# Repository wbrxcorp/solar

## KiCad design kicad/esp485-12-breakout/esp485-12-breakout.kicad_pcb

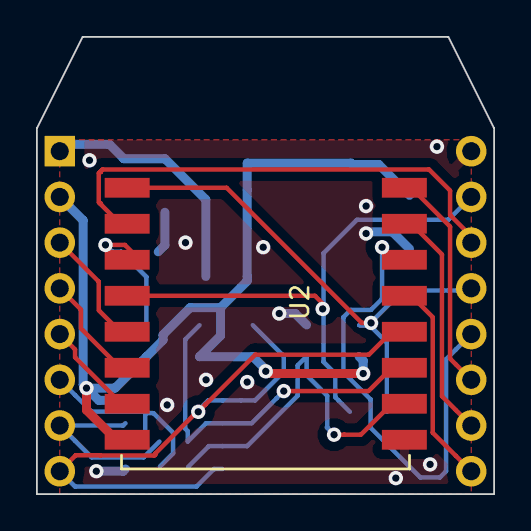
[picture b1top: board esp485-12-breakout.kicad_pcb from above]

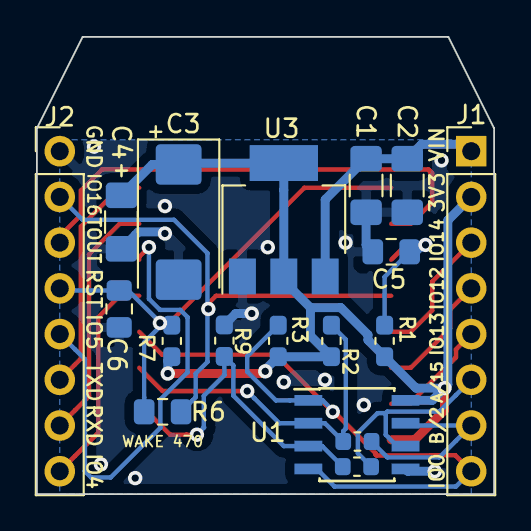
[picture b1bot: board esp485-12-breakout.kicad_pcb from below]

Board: 2 copper layers, 25.4 x 25.4 mm, 19 parts (18 on the bottom side), 19 nets.

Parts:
C1, C2, C4: C; C_1206_3216Metric_Pad1.42x1.75mm_HandSolder
C3: C; CP_EIA-7343-15_Kemet-W_Pad2.25x2.55mm_HandSolder
C5, C6: C; C_0805_2012Metric_Pad1.15x1.40mm_HandSolder
J1, J2: Conn_01x08; PinHeader_1x08_P2.54mm_Vertical
R1, R2, R3, R7, R9: 10K; R_0603_1608Metric_Pad1.05x0.95mm_HandSolder
R4, R8: 0; R_0603_1608Metric
R6: 1k; R_0805_2012Metric_Pad1.15x1.40mm_HandSolder
U1: MAX3485; SOIC-8_3.9x4.9mm_P1.27mm
U2: ESP-12; ESP-12E_SMD_NO_UNUSED_PAD
U3: AMS1117-3.3; SOT-223-3_TabPin2

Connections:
+3V3: C3.1, C4.1, J1.2, R1.1, R2.1, R3.1, R7.1, U1.8, U2.8, U3.2
A: J1.6, R4.1, U1.6
B: J1.7, R8.1, U1.7
EN: C5.1, R1.2, U2.3
GND: C1.2, C2.2, C3.2, C4.2, C5.2, C6.2, J2.1, R9.2, U1.5, U2.9, U3.1
IO0: J1.8, R3.2, U1.1, U1.4, U2.12
IO2: R2.2, R8.2, U1.2, U2.11
IO4: J2.8, U2.13
IO5: J2.5, U2.14
IO12: J1.4, U2.6
IO13: J1.5, U2.7
IO14: J1.3, U2.5
IO15: R4.2, R9.1, U1.3, U2.10
IO16: J2.2, R6.2, U2.4
RST: C6.1, J2.4, R6.1, R7.2, U2.1
RXD: J2.7, U2.15
TOUT: J2.3, U2.2
TXD: J2.6, U2.16
VCC: C1.1, C2.1, J1.1, U3.3

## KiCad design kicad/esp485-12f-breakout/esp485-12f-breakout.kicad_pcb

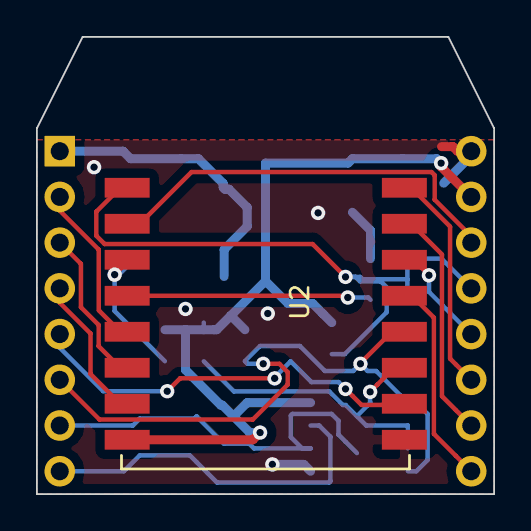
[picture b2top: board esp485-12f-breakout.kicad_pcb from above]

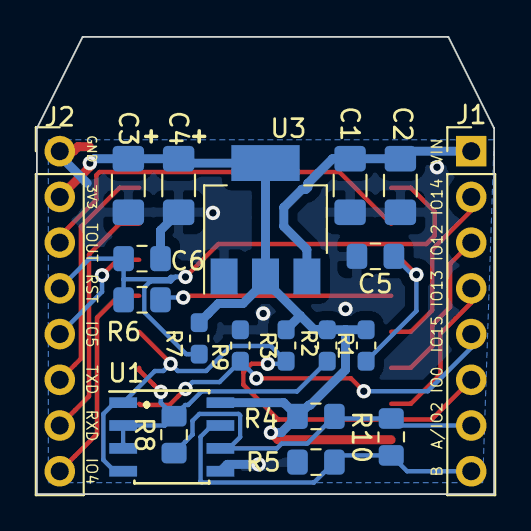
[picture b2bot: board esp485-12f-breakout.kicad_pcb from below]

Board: 2 copper layers, 25.4 x 25.4 mm, 21 parts (20 on the bottom side), 19 nets.

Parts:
C1, C2, C3, C4: C; C_1206_3216Metric_Pad1.42x1.75mm_HandSolder
C5, C6: 0.1uF; C_0805_2012Metric_Pad1.15x1.40mm_HandSolder
J1, J2: Conn_01x08; PinHeader_1x08_P2.54mm_Vertical
R1, R2, R3, R7, R9: 10K; R_0603_1608Metric_Pad1.05x0.95mm_HandSolder
R4, R5: 20K; R_0805_2012Metric_Pad1.15x1.40mm_HandSolder
R6: 1k; R_0805_2012Metric_Pad1.15x1.40mm_HandSolder
R8: 0; R_0805_2012Metric_Pad1.15x1.40mm_HandSolder
R10: 100; R_0805_2012Metric_Pad1.15x1.40mm_HandSolder
U1: MAX3485; SOIC-8_3.9x4.9mm_P1.27mm
U2: ESP-12F; ESP-12E_SMD_NO_UNUSED_PAD
U3: AMS1117-3.3; SOT-223-3_TabPin2

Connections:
+3V3: C3.1, C4.1, J2.2, R1.2, R2.1, R3.1, R4.1, R7.1, U1.8, U2.8, U3.2
/A: J1.7, R4.2, R8.1, R10.2, U1.6
/B: J1.8, R5.1, R10.1, U1.7
/EN: C5.1, R1.1, U2.3
/IO0: J1.6, R3.2, U1.1, U1.4, U2.12
/IO2: R2.2, R8.2, U1.2, U1.3, U2.11
/IO4: J2.8, U2.13
/IO5: J2.5, U2.14
/IO12: J1.3, U2.6
/IO13: J1.4, U2.7
/IO14: J1.2, U2.5
/IO15: J1.5, R9.1, U2.10
/RST: C6.1, J2.4, R6.2, R7.2, U2.1
/RXD: J2.7, U2.15
/TOUT: J2.3, U2.2
/TXD: J2.6, U2.16
GND: C1.2, C2.2, C3.2, C4.2, C5.2, C6.2, J2.1, R5.2, R9.2, U1.5, U2.9, U3.1
unnamed: R6.1, U2.4
VCC: C1.1, C2.1, J1.1, U3.3

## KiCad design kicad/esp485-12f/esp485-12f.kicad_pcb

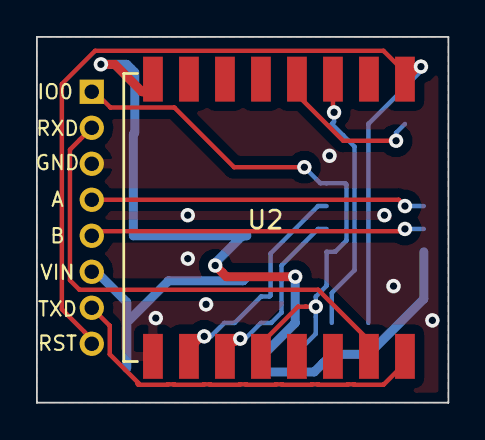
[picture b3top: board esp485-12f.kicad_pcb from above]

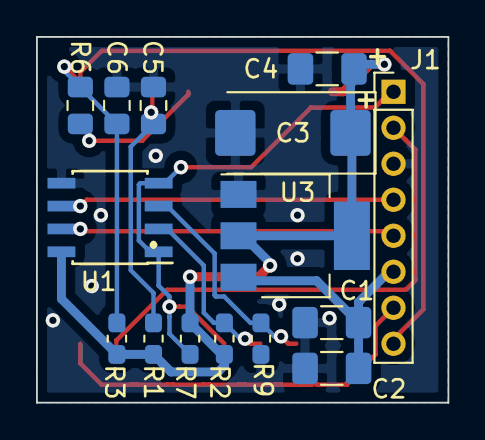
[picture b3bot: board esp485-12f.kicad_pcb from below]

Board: 2 copper layers, 22.9 x 20.3 mm, 16 parts (15 on the bottom side), 13 nets.

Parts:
C1, C2, C4: C; C_1206_3216Metric_Pad1.42x1.75mm_HandSolder
C3: C; CP_EIA-7343-15_Kemet-W_Pad2.25x2.55mm_HandSolder
C5, C6: C; C_0805_2012Metric_Pad1.15x1.40mm_HandSolder
J1: Conn_01x08; PinHeader_1x08_P2.00mm_Vertical
R1, R2, R3, R7, R9: 10K; R_0603_1608Metric_Pad1.05x0.95mm_HandSolder
R6: 1K; R_0805_2012Metric_Pad1.15x1.40mm_HandSolder
U1: MAX3485; SOIC-8_3.9x4.9mm_P1.27mm
U2: ESP-12F; ESP-12E_SMD_NO_UNUSED_PAD
U3: AMS1117-3.3; SOT-223-3_TabPin2

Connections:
+3V3: C3.1, C4.1, R1.2, R2.2, R3.2, R7.2, U1.8, U2.8, U3.2
A: J1.4, U1.6
B: J1.5, U1.7
EN: C5.1, R1.1, U2.3
GND: C1.2, C2.2, C3.2, C4.2, C5.2, C6.2, J1.3, R9.1, U1.5, U2.9, U3.1
IO0: J1.1, R7.1, U1.1, U1.4, U2.12
IO2: R2.1, U1.2, U2.11
IO15: R9.2, U1.3, U2.10
IO16: R6.2, U2.4
RST: C6.1, J1.8, R3.1, R6.1, U2.1
RXD: J1.2, U2.15
TXD: J1.7, U2.16
VCC: C1.1, C2.1, J1.6, U3.3

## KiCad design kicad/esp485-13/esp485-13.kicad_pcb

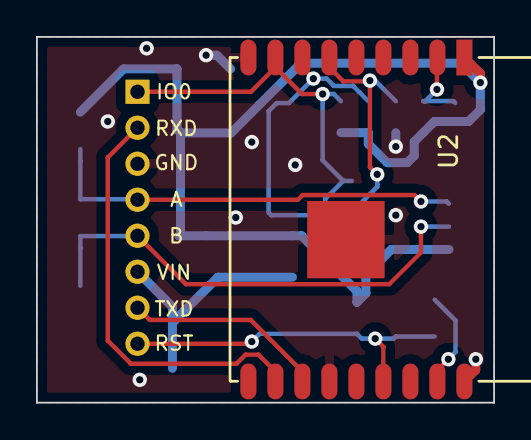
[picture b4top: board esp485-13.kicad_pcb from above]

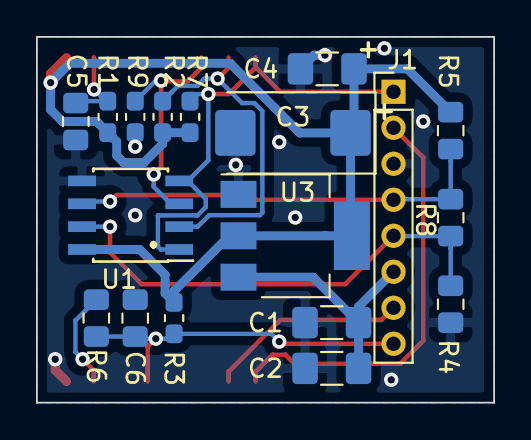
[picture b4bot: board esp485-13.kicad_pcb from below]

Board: 2 copper layers, 25.4 x 20.3 mm, 19 parts (18 on the bottom side), 13 nets.

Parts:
C1, C2, C4: C; C_1206_3216Metric_Pad1.42x1.75mm_HandSolder
C3: C; CP_EIA-7343-15_Kemet-W_Pad2.25x2.55mm_HandSolder
C5, C6: C; C_0805_2012Metric_Pad1.15x1.40mm_HandSolder
J1: Conn_01x08; PinHeader_1x08_P2.00mm_Vertical
R1, R2, R3, R7, R9: 10K; R_0603_1608Metric_Pad1.05x0.95mm_HandSolder
R4, R5, R6: 1K; R_0805_2012Metric_Pad1.15x1.40mm_HandSolder
R8: 120; R_0805_2012Metric_Pad1.15x1.40mm_HandSolder
U1: MAX3485; SOIC-8_3.9x4.9mm_P1.27mm
U2: ESP-WROOM-02; ESP-13-WROOM-02
U3: AMS1117-3.3; SOT-223-3_TabPin2

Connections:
+3V3: C3.1, C4.1, R1.2, R2.2, R3.2, R5.2, R7.2, U1.8, U2.1, U3.2
A: J1.4, R5.1, R8.2, U1.6
B: J1.5, R4.1, R8.1, U1.7
EN: C5.1, R1.1, U2.2
GND: C1.2, C2.2, C3.2, C4.2, C5.2, C6.2, J1.3, R4.2, R9.1, U1.5, U2.9, U2.13, U2.18, U2.PAD, U3.1
IO0: J1.1, R7.1, U1.1, U1.4, U2.8
IO2: R2.1, U1.2, U2.7
IO15: R9.2, U1.3, U2.6
IO16: R6.2, U2.17
RST: C6.1, J1.8, R3.1, R6.1, U2.15
RXD: J1.2, U2.11
TXD: J1.7, U2.12
VCC: C1.1, C2.1, J1.6, U3.3

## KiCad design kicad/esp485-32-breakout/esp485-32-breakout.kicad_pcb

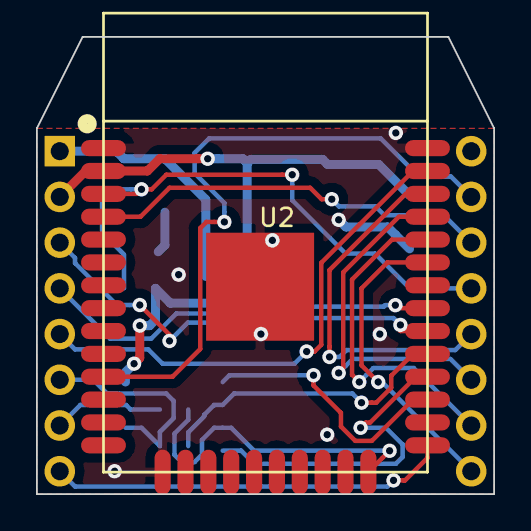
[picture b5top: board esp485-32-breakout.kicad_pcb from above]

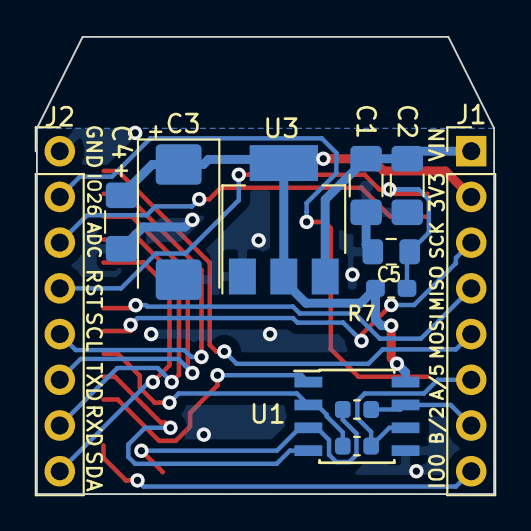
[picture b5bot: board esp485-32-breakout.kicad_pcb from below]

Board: 2 copper layers, 25.4 x 25.4 mm, 13 parts (12 on the bottom side), 20 nets.

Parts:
C1, C2, C4: C; C_1206_3216Metric_Pad1.42x1.75mm_HandSolder
C3: C; CP_EIA-7343-15_Kemet-W_Pad2.25x2.55mm_HandSolder
C5: C; C_0805_2012Metric_Pad1.15x1.40mm_HandSolder
J1, J2: Conn_01x08; PinHeader_1x08_P2.54mm_Vertical
R4, R8: 0; R_0603_1608Metric
R7: 10K; R_0603_1608Metric_Pad1.05x0.95mm_HandSolder
U1: MAX3485; SOIC-8_3.9x4.9mm_P1.27mm
U2: ESP-WROOM-32; ESP32-WROOM
U3: AMS1117-3.3; SOT-223-3_TabPin2

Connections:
+3V3: C3.1, C4.1, J1.2, R7.1, U1.8, U2.2, U3.2
/IO16: U1.1, U2.27
/IO17: U1.4, U2.28
A: J1.6, R4.1, U1.6
ADC: J2.3, U2.4
B: J1.7, R8.1, U1.7
GND: C1.2, C2.2, C3.2, C4.2, C5.2, J2.1, U1.5, U2.1, U2.15, U2.38, U2.39, U3.1
IO0: J1.8, U2.25
IO2: R8.2, U1.3, U2.24
IO5: R4.2, U1.2, U2.29
IO26: J2.2, U2.11
MISO: J1.4, U2.31
MOSI: J1.5, U2.37
RST: C5.1, J2.4, R7.2, U2.3
RXD: J2.7, U2.34
SCK: J1.3, U2.30
SCL: J2.5, U2.36
SDA: J2.8, U2.33
TXD: J2.6, U2.35
VCC: C1.1, C2.1, J1.1, U3.3

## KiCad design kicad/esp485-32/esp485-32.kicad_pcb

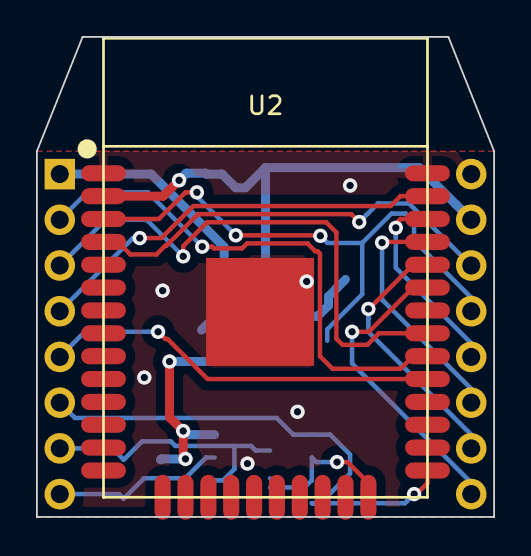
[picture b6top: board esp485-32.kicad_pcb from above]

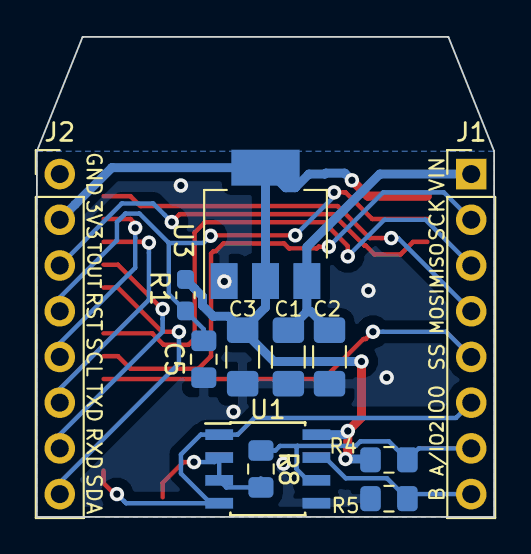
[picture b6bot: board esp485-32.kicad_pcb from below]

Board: 2 copper layers, 25.4 x 26.7 mm, 13 parts (12 on the bottom side), 17 nets.

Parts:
C1, C2, C3: C; C_1206_3216Metric_Pad1.42x1.75mm_HandSolder
C5: C; C_0805_2012Metric_Pad1.15x1.40mm_HandSolder
J1, J2: Conn_01x08; PinHeader_1x08_P2.54mm_Vertical
R1: 10K; R_0603_1608Metric_Pad1.05x0.95mm_HandSolder
R4, R5: 20K; R_0805_2012Metric_Pad1.15x1.40mm_HandSolder
R8: 0; R_0805_2012Metric_Pad1.15x1.40mm_HandSolder
U1: MAX3485; SOIC-8_3.9x4.9mm_P1.27mm
U2: ESP32-WROOM
U3: ADP3338-3.3; SOT-223-3_TabPin2

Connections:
+3V3: C3.1, J2.2, R1.2, R4.2, U1.8, U2.2, U3.2
A: J1.7, R4.1, R8.1, U1.6
B: J1.8, R5.2, U1.7
GND: C1.2, C2.2, C3.2, C5.2, J2.1, R5.1, U1.5, U2.1, U2.38, U2.39, U3.1
IO0: J1.6, U1.1, U1.4, U2.25
IO2: R8.2, U1.2, U1.3, U2.24
MISO: J1.3, U2.31
MOSI: J1.4, U2.37
RST: C5.1, J2.4, R1.1, U2.3
RXD: J2.7, U2.34
SCK: J1.2, U2.30
SCL: J2.5, U2.36
SDA: J2.8, U2.33
SS: J1.5, U2.29
TOUT: J2.3, U2.4
TXD: J2.6, U2.35
VCC: C1.1, C2.1, J1.1, U3.3

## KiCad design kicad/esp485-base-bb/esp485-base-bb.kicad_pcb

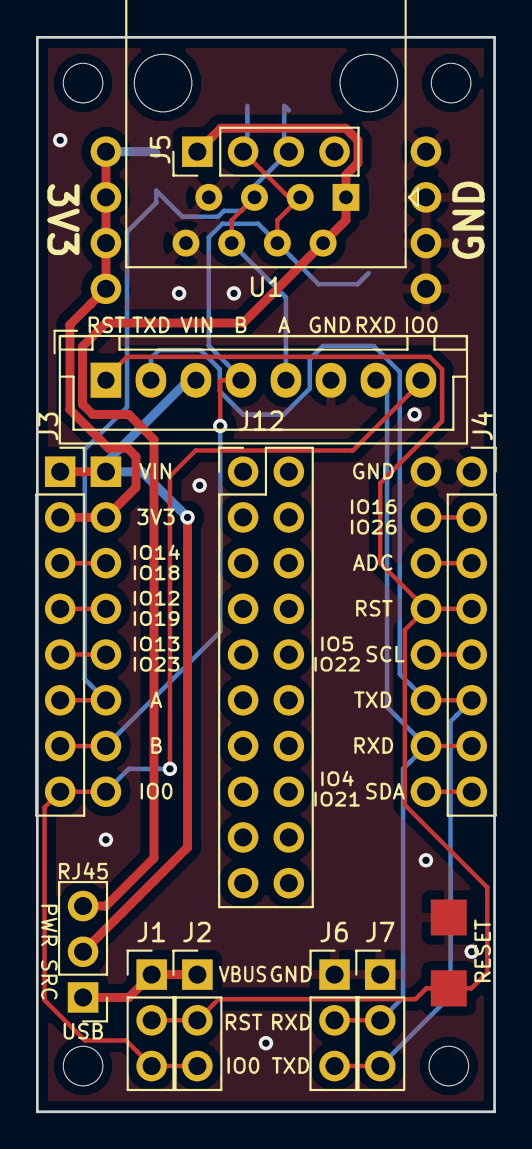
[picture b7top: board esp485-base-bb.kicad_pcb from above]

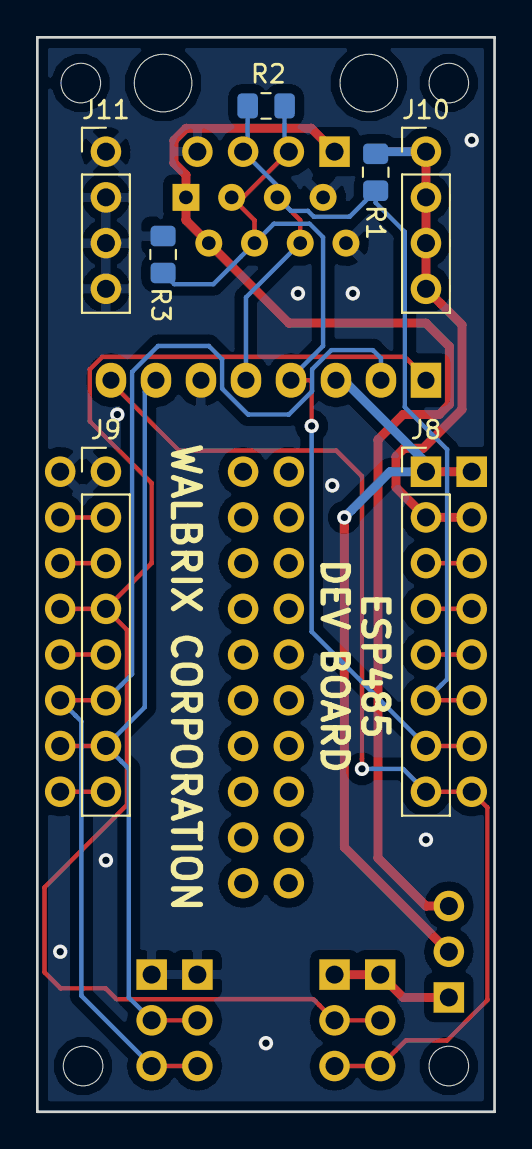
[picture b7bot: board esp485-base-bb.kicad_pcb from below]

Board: 2 copper layers, 25.4 x 59.7 mm, 18 parts (7 on the bottom side), 18 nets.

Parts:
J1, J2, J6, J7: Conn_01x03; PinHeader_1x03_P2.54mm_Vertical
J3, J4: Conn_01x08; PinSocket_1x08_P2.54mm_Vertical
J5, J10, J11: Conn_01x04; PinHeader_1x04_P2.54mm_Vertical
J8, J9: Conn_01x08; PinHeader_1x08_P2.54mm_Vertical
J12: Conn_01x08; JST_XH_B08B-XH-A_1x08_P2.50mm_Vertical
R1, R3: 1K; R_0805_2012Metric_Pad1.15x1.40mm_HandSolder
R2: 120; R_0805_2012Metric_Pad1.15x1.40mm_HandSolder
SW1: SW_SPDT; PinHeader_1x03_P2.54mm_Vertical
SW2: SW_Push; tactile_switch_smd_4x3mm_2p
U1: RJ45; RJ45_Amphenol_54602-x08_Horizontal

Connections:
+3V3: J3.2, J8.2, J10.1, J10.2, J10.3, J10.4, R1.1
/A: J3.6, J5.3, J8.6, J12.5, R1.2, R2.2, U1.5, U1.6
/B: J3.7, J5.2, J8.7, J12.4, R2.1, R3.1, U1.3, U1.4
/IO0: J1.3, J2.3, J3.8, J8.8, J12.8
/IO4: J4.8, J9.8
/IO5: J4.5, J9.5
/IO12: J3.4, J8.4
/IO13: J3.5, J8.5
/IO14: J3.3, J8.3
/IO16: J4.2, J9.2
/RST: J1.2, J2.2, J4.4, J9.4, J12.1, SW2.1
/RXD: J4.7, J6.2, J7.2, J9.7, J12.7
/TOUT: J4.3, J9.3
/TXD: J4.6, J6.3, J7.3, J9.6, J12.2
/VBUS: J1.1, J2.1, SW1.1
/VIN: J3.1, J8.1, J12.3, SW1.2
GND: J4.1, J5.4, J6.1, J7.1, J9.1, J11.1, J11.2, J11.3, J11.4, J12.6, R3.2, SW2.2, U1.7, U1.8
VCC: J5.1, SW1.3, U1.1, U1.2
